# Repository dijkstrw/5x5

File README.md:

5x5 aka Gojira!
===============

This is my first custom keyboard, a 5x5 cherry mx matrix based on the STM32F1
with libopencm3. The project contains firmware, schematics and a board layout
in kicad.

This project is intended as a platform for custom keyboard development. It
supports:
- usb keyboard scancodes
- bios boot and nkro
- system / consumer codes
- generation of mouse events
- usb serial interface
- an automouse mode for fast-clicking
- programmable macro keys via serial
- storing current configuration in "userflash"

The board is programmed using a 6-pin TagConnect, that must be wired
to a STM Discovery SWD/STLink programming port.

Building
========

    git submodule init
    git submodule update
    make -C libopencm3
    make

Features
========

Keyboards
---------

The board provides 3 types of keyboards via different usb
endpoints.

1. The first is the usb standard bios keyboard definition, which
   allows the keyboard also to emit key codes to hosts with limited
   usb hid support. (This used to be the case in <2015 style bioses,
   hence the name.)

2. The second keyboard is a n-key-rollover, which exposes a keyboard
   that allows 224 usb keyboard scancodes to be pressed
   simultaneously. Also, because we do not need to adhere to the bios
   boot standard, this endpoint's interval can set much lower = it
   types much faster.

3. The third keyboard can emit so called consumer and system
   codes. Example consumer key codes are PLAY, PAUSE, but also MARK,
   CLEARMARK, REPEATFROMMARK. So everything the typical multimedia
   keys emit and then some.

Mouse
-----

Operate the rodent from your keyboard! There is support for x, y, 5
buttons and a vertical and horizontal scrollwheel action.

Serial
------

The board exposes a serial port for logging, and
configuration. Commands available are:

    ? - show a terse description of available commands.

    i - show usb info strings; contains the git-describe tag of the
        current firmware, so mission critical to some, useless to
        everybody else.

    d - dump the keymap(s).

    K - redefine a key in the keymap, takes a hexadecimal argument of
        the form <layer><row><column><type><arg1><arg2><arg3>, with each
        argument being 2 digits long.

    m - clear all macro keys.

    M - define one macro key, takes an argument of the form
        <number><oftenusedstring>. The number is a two hexdigits, the
        string can be upto 32 7-bit ascii chars long and is terminated
        with a newline.

    n - set keyboard mode to bios (default).

    N - set keyboard mode to nkro.

    R - read configuration from flash

    W - write configuration to flash

    Z - clear the configration flash, revert to "factory" keymap at
        next powerup.

Command interpretation starts after receiving a newline.

Automouse
---------

Automouse is a mouse clicker, with optional speed setting and wiggle
amounts. This allows you to click real fast, and wiggle the mouse
while using your hands for something else.

Macros
------

Macros set via serial are lost at power off unless the configuration
is written to flash. Loading from flash happens automatically at
powerup.

The strings that you provide via serial need to be translated into usb
keycodes, so currently only 7-bit ascii strings are supported.

Setting macros via the shell is easy:

    echo -e "\nM01Nevergonnagiveyouup!\n" > /dev/ttyACM0

Notes:

- The initial newline is a trick to make sure our M will be considered
  the start of a command, no matter what has been put to the serial
  before by you, some driver or the os.
- This particular example defines the macro for macro key number 1.
- You need to have a macro key 1 in your keymap, otherwise you have
  nothing to trigger the macro.

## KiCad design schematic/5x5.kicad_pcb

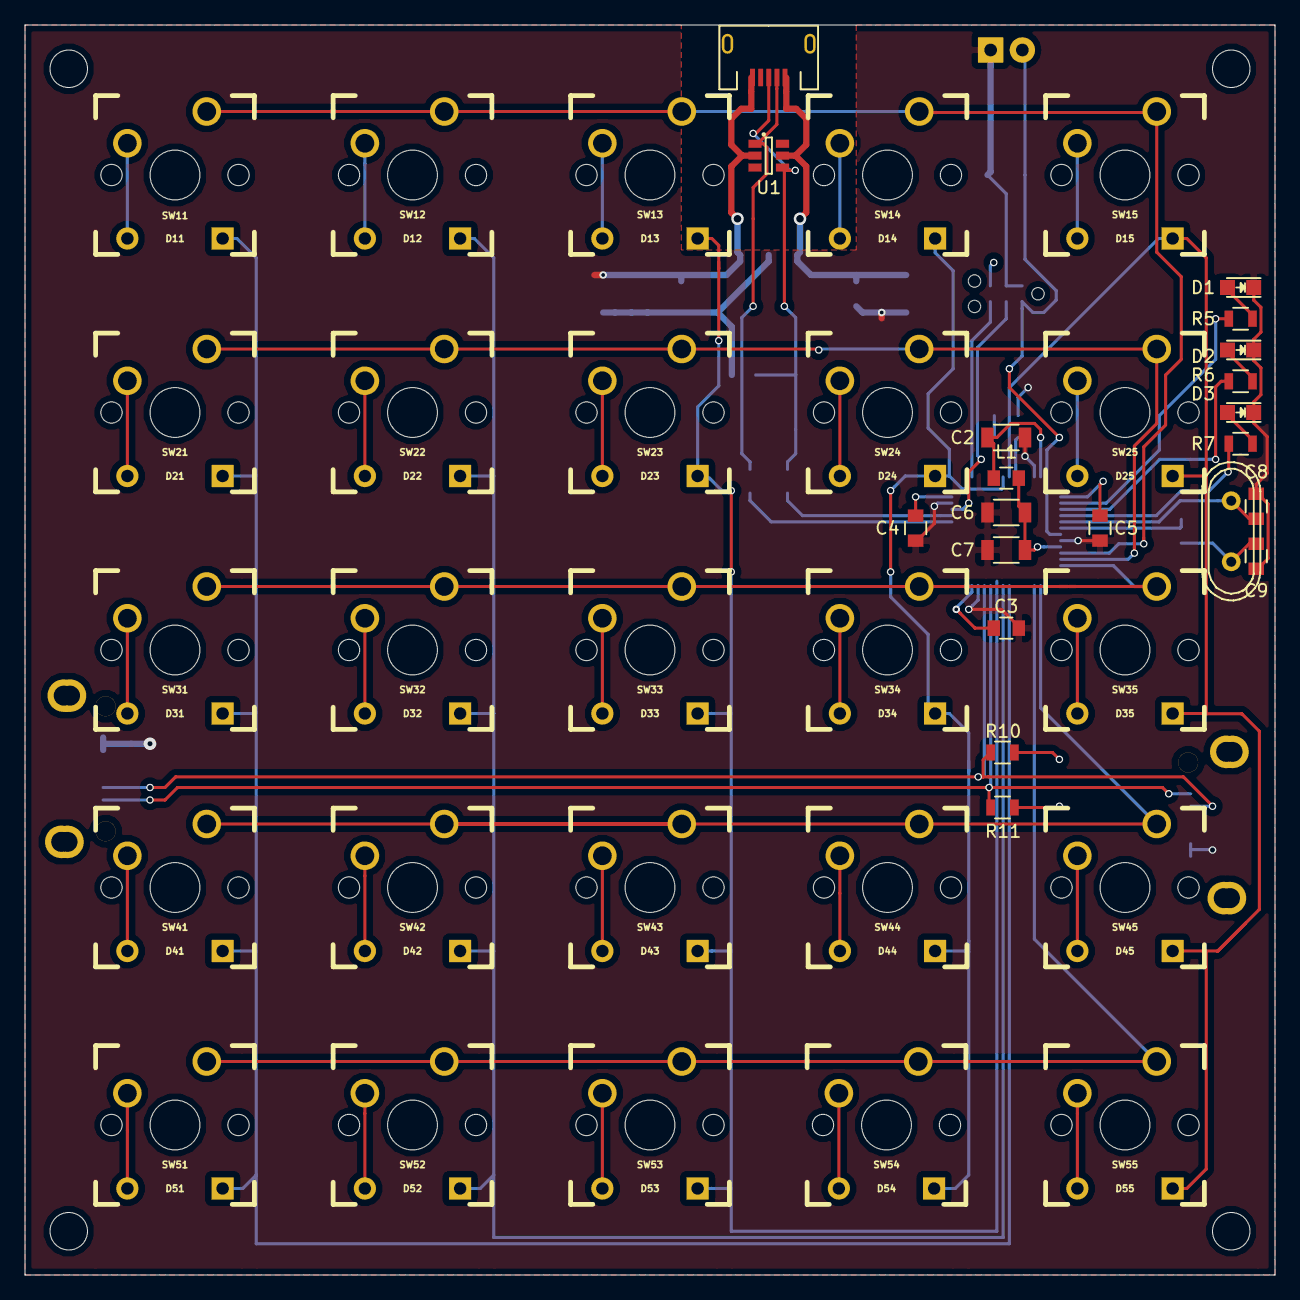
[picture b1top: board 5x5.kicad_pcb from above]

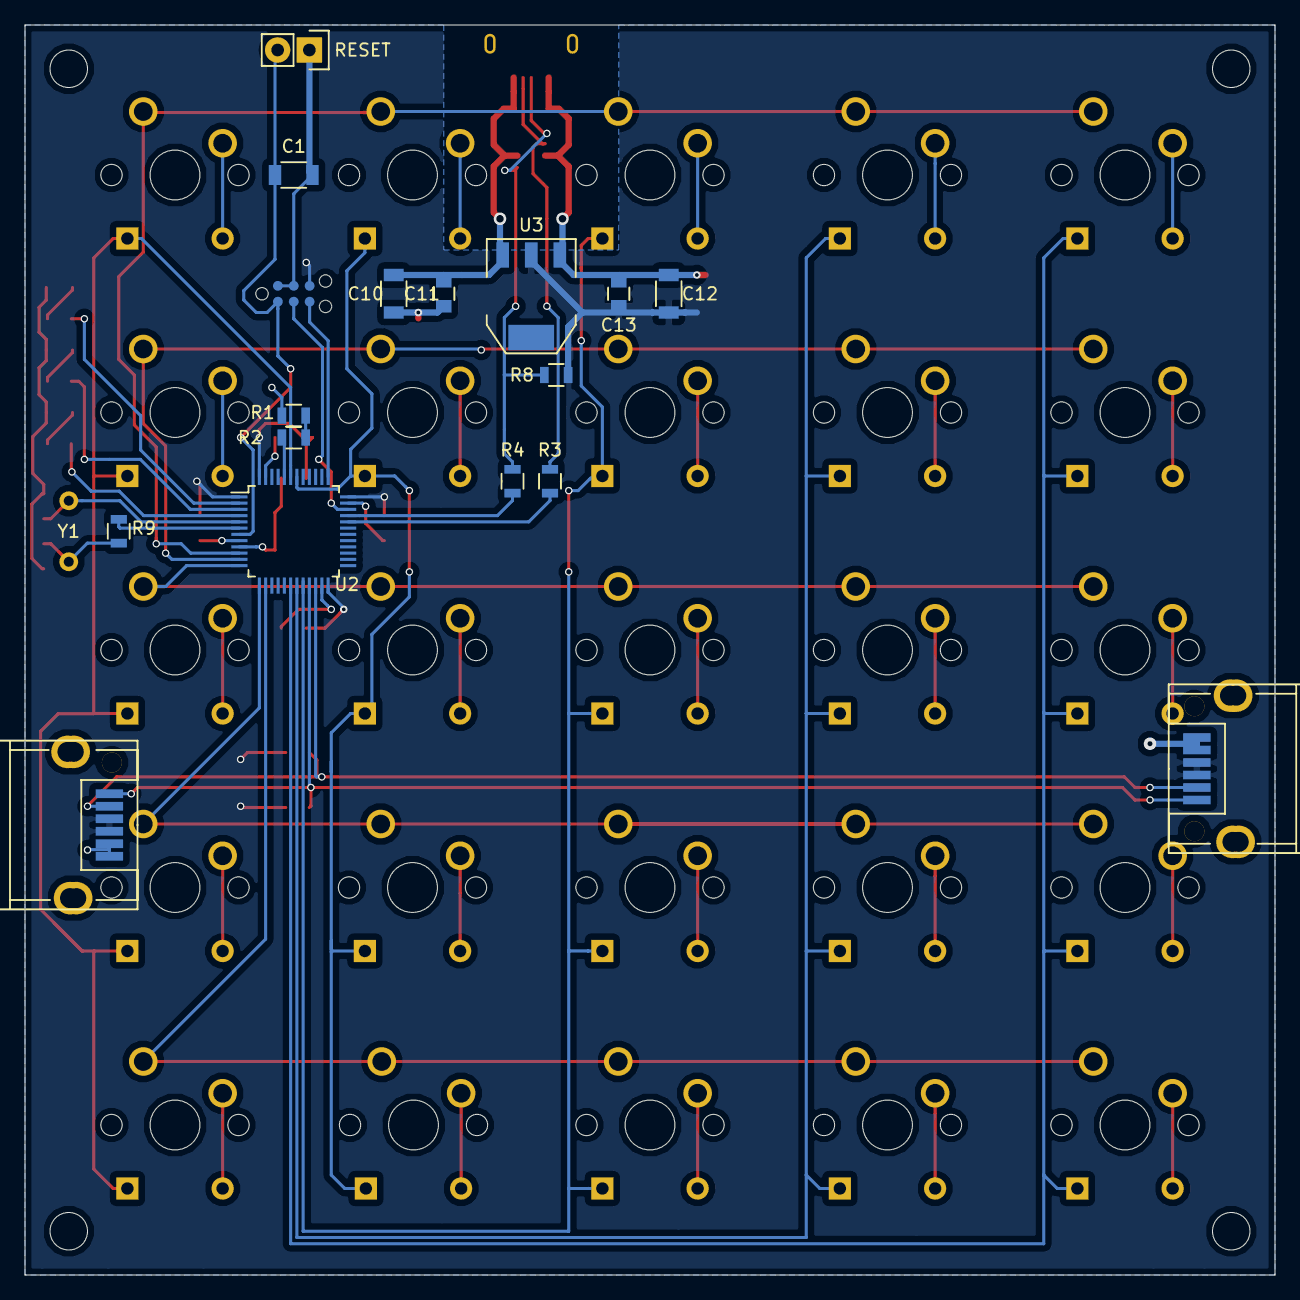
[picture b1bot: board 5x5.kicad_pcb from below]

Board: 2 copper layers, 100.0 x 100.0 mm, 87 parts (17 on the bottom side), 59 nets.

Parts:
C1: 100n; C_1206
C2, C12: 10u; C_1206
C3, C4, C5, C11, C13: 100n; C_0805
C6, C10: 1u; C_1206
C7: 1n; C_1206
C8, C9: 20p; C_0805
D1, D2, D3: Led_Small; LED-0805
D11, D12, D13, D14, D15, D21, D22, D23, D24, D25, D31, D32, D33, D34, D35, D41, D42, D43, D44, D45, D51, D52, D53, D54, D55: 1N4148; CHERRY_MX_DIODE
L1: bead; C_0805
P1: JTAG_SWDP; TC2030-IDC-NL
P2: USB-B; FCI-10118193-0001LF
P5: I2CI; Harwin-M702-230642
P6: I2CO; Harwin-M702-230642
R1: 10k; R_0805
R2: 0; R_0805
R3, R4: 22; R_0805
R5, R6, R7: 1k; R_0805
R8: 1k5; R_0805
R9: 33; R_0805
R10, R11: 4k7; R_0805
RESET: SW; Pin_Header_Straight_1x02
SW11, SW12, SW13, SW14, SW15, SW21, SW22, SW23, SW24, SW25, SW31, SW32, SW33, SW34, SW35, SW41, SW42, SW43, SW44, SW45, SW51, SW52, SW53, SW54, SW55: SW; CHERRY_PCB_100H
U1: MAX3207E; SOT-23-6
U2: STM32F103C8; LQFP-48_7x7mm_Pitch0.5mm
U3: LD1117S33CTR; SOT-223
Y1: 16M; Crystal_HC49-U_Vertical

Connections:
+3V3: C2.1, C3.1, C4.1, C5.1, C12.1, C13.1, L1.1, P1.6, P5.3, P5.4, P6.3, P6.4, R8.2, R10.2, R11.2, U2.1, U2.24, U2.36, U2.48, U3.2
COL1: D11.1, D21.1, D31.1, D41.1, D51.1, U2.18
COL2: D12.1, D22.1, D32.1, D42.1, D52.1, U2.19
COL3: D13.1, D23.1, D33.1, D43.1, D53.1, U2.20
COL4: D14.1, D24.1, D34.1, D44.1, D54.1, U2.42
COL5: D15.1, D25.1, D35.1, D45.1, D55.1, U2.43
GND: C1.2, C2.2, C3.2, C4.2, C5.2, C6.2, C7.2, C8.1, C9.1, C10.2, C11.2, C12.2, C13.2, D1.1, D2.1, D3.1, P1.2, P1.4, P2.5, P5.5, P5.6, P6.5, P6.6, R2.2, RESET.1, U1.2, U2.8, U2.23, U2.35, U2.47, U3.1
unnamed: C1.1, P1.1, RESET.2, U2.7
unnamed: C6.1, C7.1, L1.2, U2.9
unnamed: C8.2, U2.5, Y1.1
unnamed: C9.2, R9.1, Y1.2
unnamed: D1.2, R5.1
unnamed: D2.2, R6.1
unnamed: D3.2, R7.1
unnamed: D11.2, SW11.2
unnamed: D12.2, SW12.2
unnamed: D13.2, SW13.2
unnamed: D14.2, SW14.2
unnamed: D15.2, SW15.2
unnamed: D21.2, SW21.2
unnamed: D22.2, SW22.2
unnamed: D23.2, SW23.2
unnamed: D24.2, SW24.2
unnamed: D25.2, SW25.2
unnamed: D31.2, SW31.2
unnamed: D32.2, SW32.2
unnamed: D33.2, SW33.2
unnamed: D34.2, SW34.2
unnamed: D35.2, SW35.2
unnamed: D41.2, SW41.2
unnamed: D42.2, SW42.2
unnamed: D43.2, SW43.2
unnamed: D44.2, SW44.2
unnamed: D45.2, SW45.2
unnamed: D51.2, SW51.2
unnamed: D52.2, SW52.2
unnamed: D53.2, SW53.2
unnamed: D54.2, SW54.2
unnamed: D55.2, SW55.2
unnamed: P1.3, U2.34
unnamed: P1.5, U2.37
unnamed: P2.2, R3.2, U1.1
unnamed: P2.3, R4.2, R8.1, U1.4
unnamed: R1.1, U2.44
unnamed: R1.2, R2.1
unnamed: R3.1, U2.32
unnamed: R4.1, U2.33
unnamed: R5.2, U2.2
unnamed: R6.2, U2.3
unnamed: R7.2, U2.4
unnamed: R9.2, U2.6
ROW1: SW11.1, SW12.1, SW13.1, SW14.1, SW15.1, U2.10
ROW2: SW21.1, SW22.1, SW23.1, SW24.1, SW25.1, U2.11
ROW3: SW31.1, SW32.1, SW33.1, SW34.1, SW35.1, U2.12
ROW4: SW41.1, SW42.1, SW43.1, SW44.1, SW45.1, U2.13
ROW5: SW51.1, SW52.1, SW53.1, SW54.1, SW55.1, U2.14
SCL: P5.1, P6.1, R11.1, U2.21
SDA: P5.2, P6.2, R10.1, U2.22
Vusb: C10.1, C11.1, P2.1, U1.5, U3.3

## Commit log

2016-04-23 Document usbreset better
2021-11-22 Better usb interface and added macro keys, and a command channel
    The usb enumeration required all interface to be enumerated before
    freeing the stack to do keyboard interactions. The trouble with this
    approach is that:
    - linux console does not require a mouse, and does not configure that
    interface
    - windows requires a driver for the serial port, and does not
2021-11-22 Adjust Makefile to newer libopencm3
2021-11-26 Better cdcacm serial host attach/detach & update readme
    - After looking at stty I noticed that if echo of input is desired
    this can easily be set on the tty. serial.c no longer echos input.
    - Detaching from serial could lead to malformed packets on the
    "out" (note usb host orientation) endpoint. Now we detect an error
    condition, and clear that without looking at the random buffer.
    - All this makes setting the macros easier, but there are still some
2021-12-04 Ammend README.md to explain macro def better
    Comment was that it seemed that macro only supported lowercase
    letters, and while there is clearly more to 7 bit ascii, why make
    people think when I can show that it is not so.
    (man ascii FTW)
2021-12-04 Forgotten define in map_ascii.h
    So checked all other .h files for style also.
2021-12-04 Move to isr driven usb interaction
2021-12-04 Prevent enumeration during bootup
    We now pull down the dp usb pin to disable host enumeration while
    starting up. This reduces the amount of errors during usb attach phase
    + can (in Linux) clear the error status of an usb port.
2021-12-05 Add USB Interface Association Descriptor (IAD). Required for Windows and probably Mac.
2021-12-05 Allow for multiple key modifiers
2022-01-07 Improve USB suspend handling
    I misunderstood usb suspend semantics; it is used to indicate that the
    host has had no communication for us for more than 3ms and that we are
    ok to go to a lower power state.
    This does not change the fact that we might have something to say to
    the host. So even in lower power state, we should keep monitoring our
    keys/mouse and issue a "remote wakeup" when such an event occurs.
2022-01-08 Improve usb reset handling
    An usb reset is signalled by the host to (re)start
    enumeration. Enumeration is now a process that:
    - can be (re)started at any time
    - must complete successfully for some of our endpoints, otherwise a
    system reset is forced
    - will halt all normal usb event posting
2022-01-08 Make led configuration part of config.h
    Currently we have 3 leds which can be set from;
    - keyboard by usb host updates
    - automouse to indicate automouse running
    - macro to indicate macro running
    And each clobbers the other. automouse and macro now only reset the
    leds that they twiddled with.
2022-04-01 WIP: adding a flash command
    Adjust the top 4k of flash to be user flash for keyboard
    configuration.
    The flash interface has a per-byte interface, and needs to be started
    and stopped.
    For writing to flash follow this procedure:
    - flash_write_start - unlock and erase flash, setup char interface
2022-04-03 User flash actions simplified
    User flashing of configuration is now managed in two functions:
    flash_read_config and flash_write_config.
    The previous interface was too fragile and took a lot more code. This
    new approach captures the actual structures in flash in terms of
    structs. This allows the compiler to check our bounds during
    compilation.
